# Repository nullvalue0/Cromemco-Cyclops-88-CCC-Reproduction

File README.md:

This is an attempt to reproduce the PCB's for the Cromemco Cyclops digital camera, the 2-board set "88 CCC". The original digital cameras are basically impossible to find. Thankfully there has already been a [reproduction effort for the camera itself](http://wsudbrink.dyndns.org:8080/cyclops/index.html).

The next missing piece then would be the controller boards. While a few of the 88 CCC's have turned up, they are mainly already in collectors hands and still very rare. In several years of trying to find them I haven't been able to nab a set.

With the [Dazzler boards already successfully reproduced](https://forum.vcfed.org/index.php?threads/cromemco-dazzler-replica-project.77906), this seems like a great next project. I'll update this readme as the project progresses.

The 'Original Images' folder contains pictures of the original board set that I've found on various sites.

The 'Original Schematics' folder contains the original manual & schematics for the 88 CCC. I've combined the 2-page schematic into a single image for each board, making it much easier to reference.

The PCB folder will contain the reproduction Kicad files & gerbers for both S-100 boards.

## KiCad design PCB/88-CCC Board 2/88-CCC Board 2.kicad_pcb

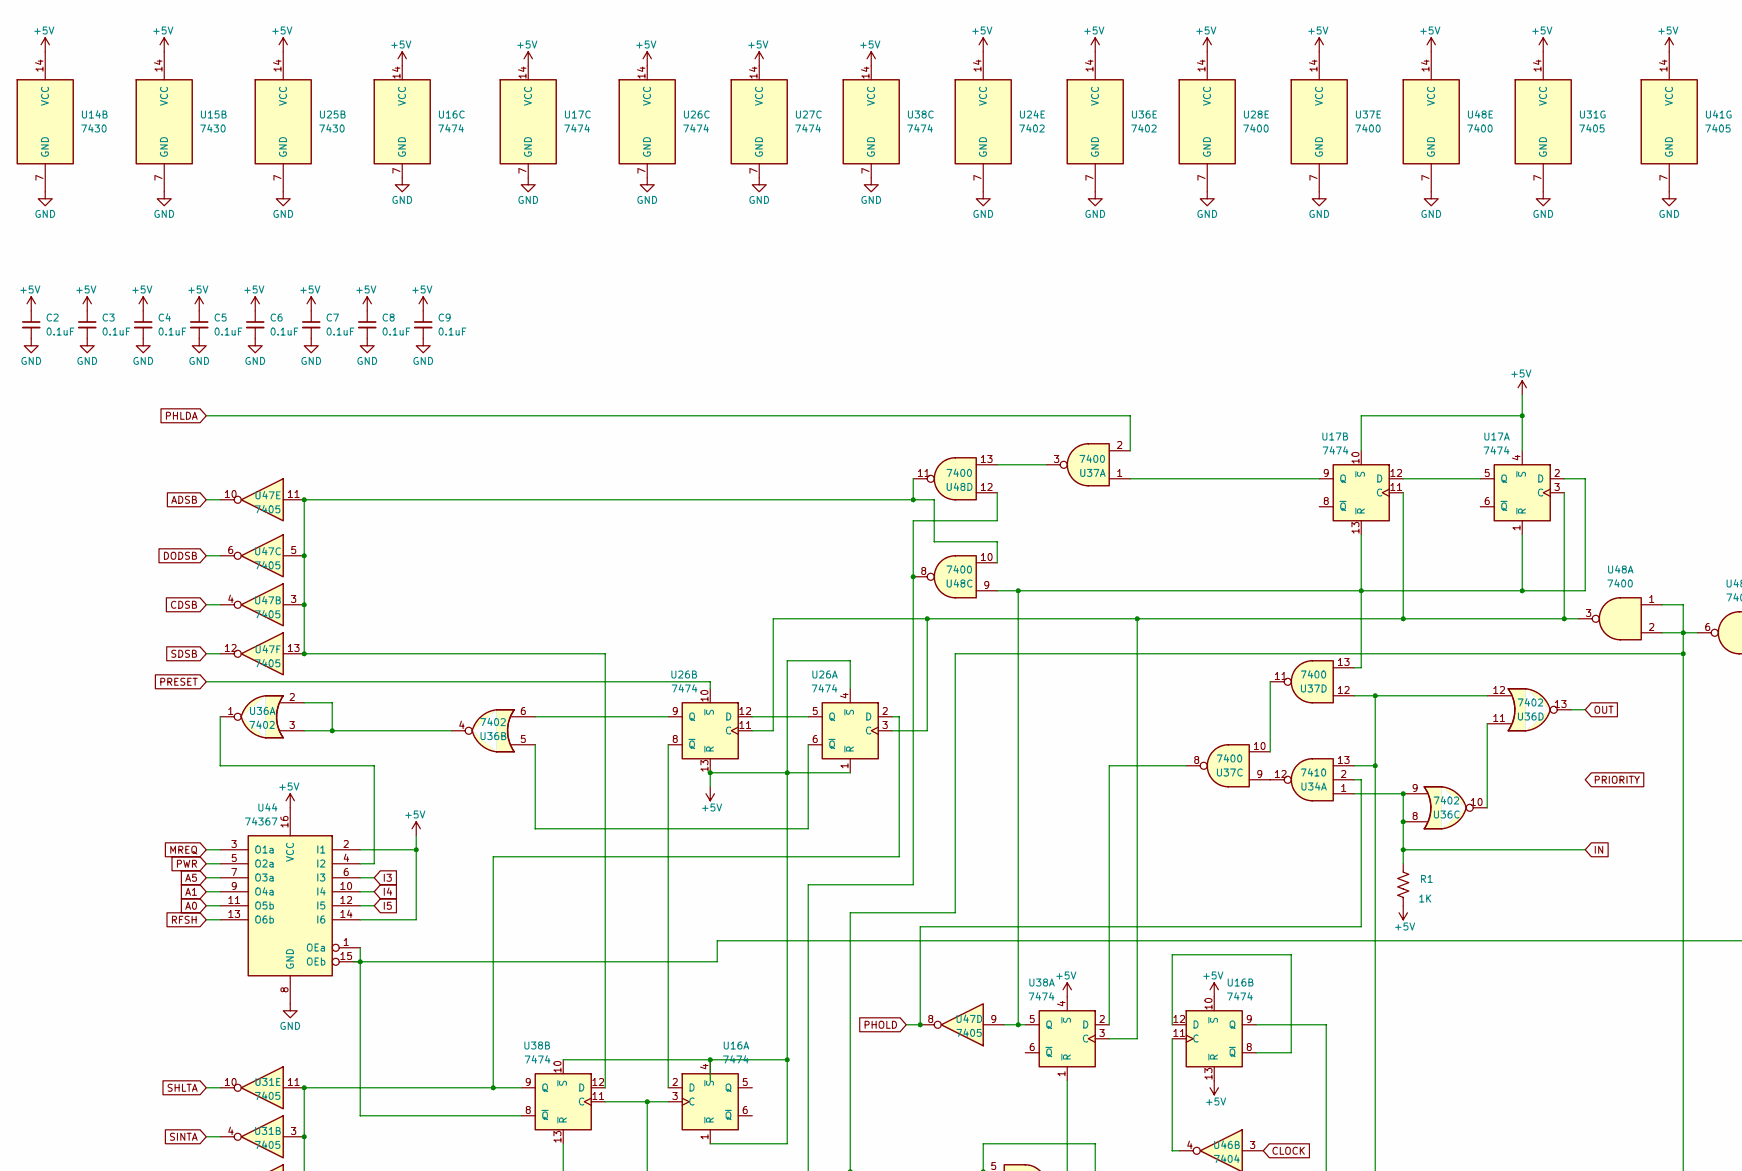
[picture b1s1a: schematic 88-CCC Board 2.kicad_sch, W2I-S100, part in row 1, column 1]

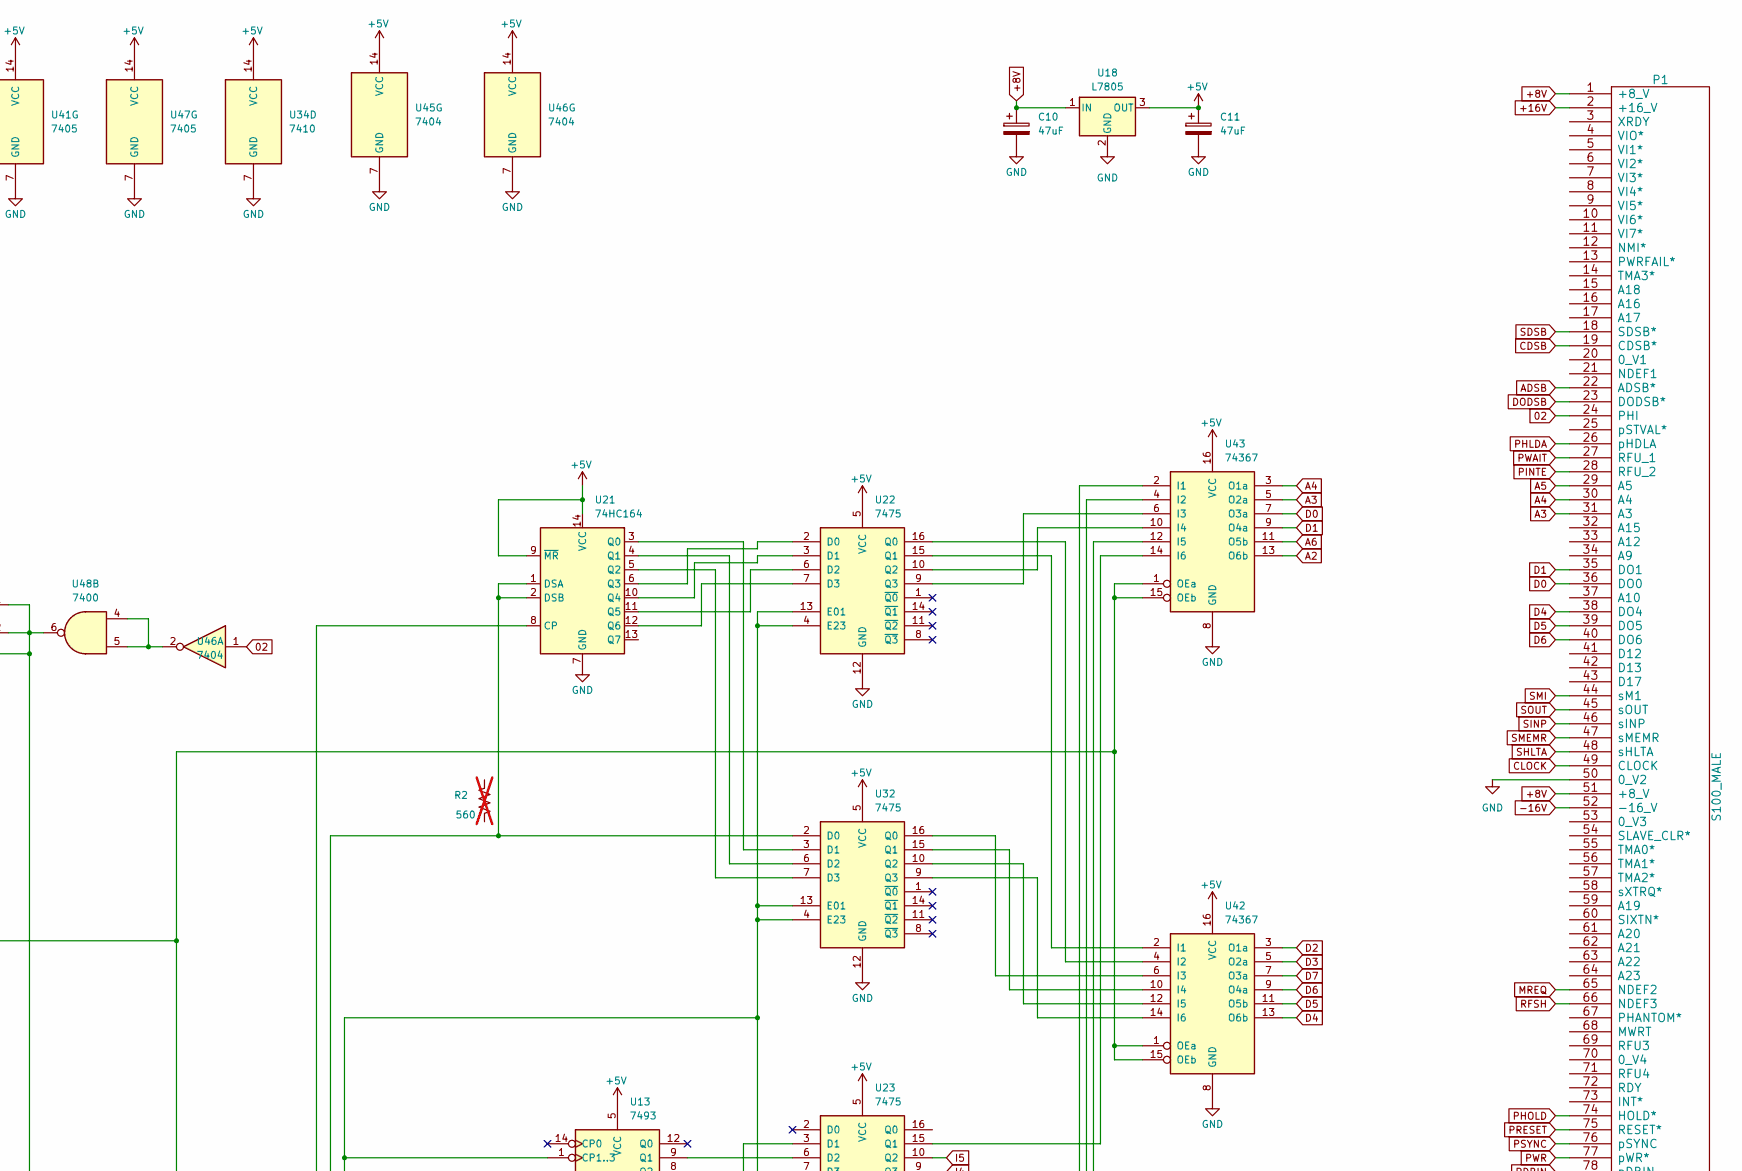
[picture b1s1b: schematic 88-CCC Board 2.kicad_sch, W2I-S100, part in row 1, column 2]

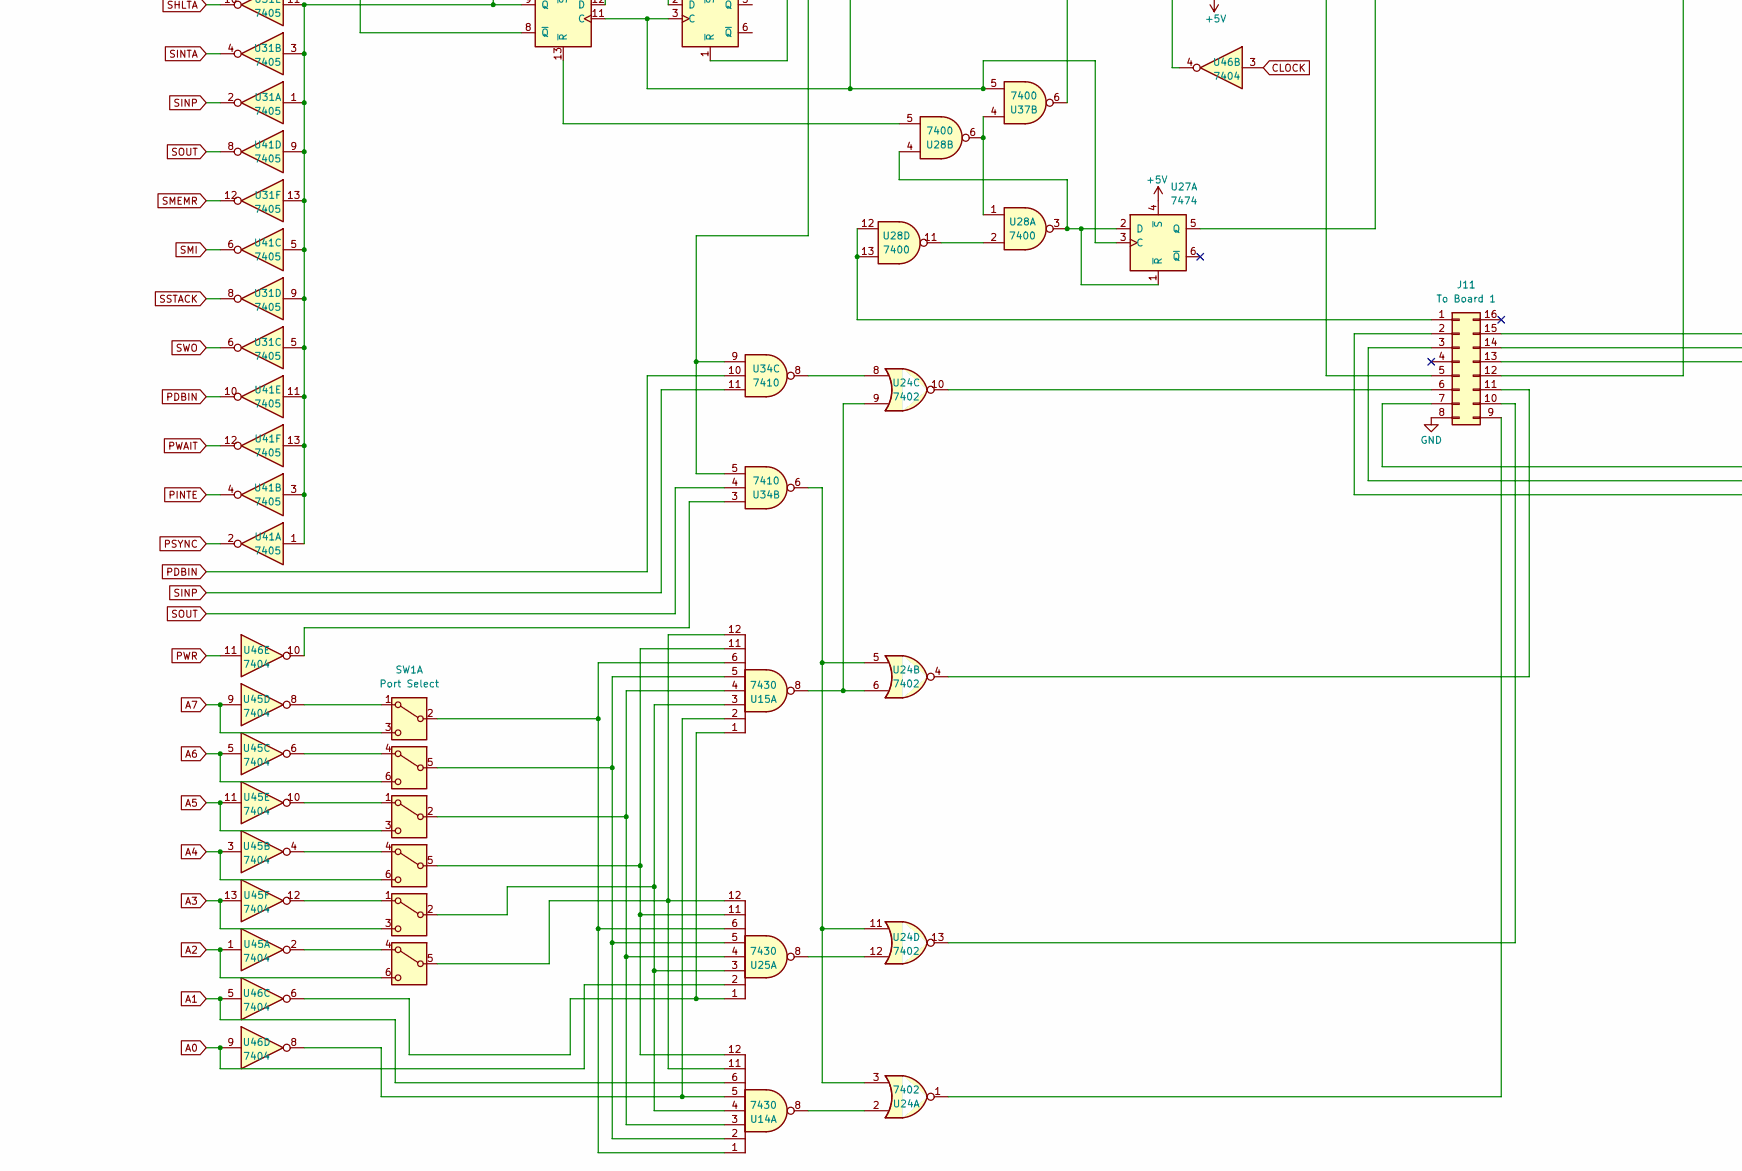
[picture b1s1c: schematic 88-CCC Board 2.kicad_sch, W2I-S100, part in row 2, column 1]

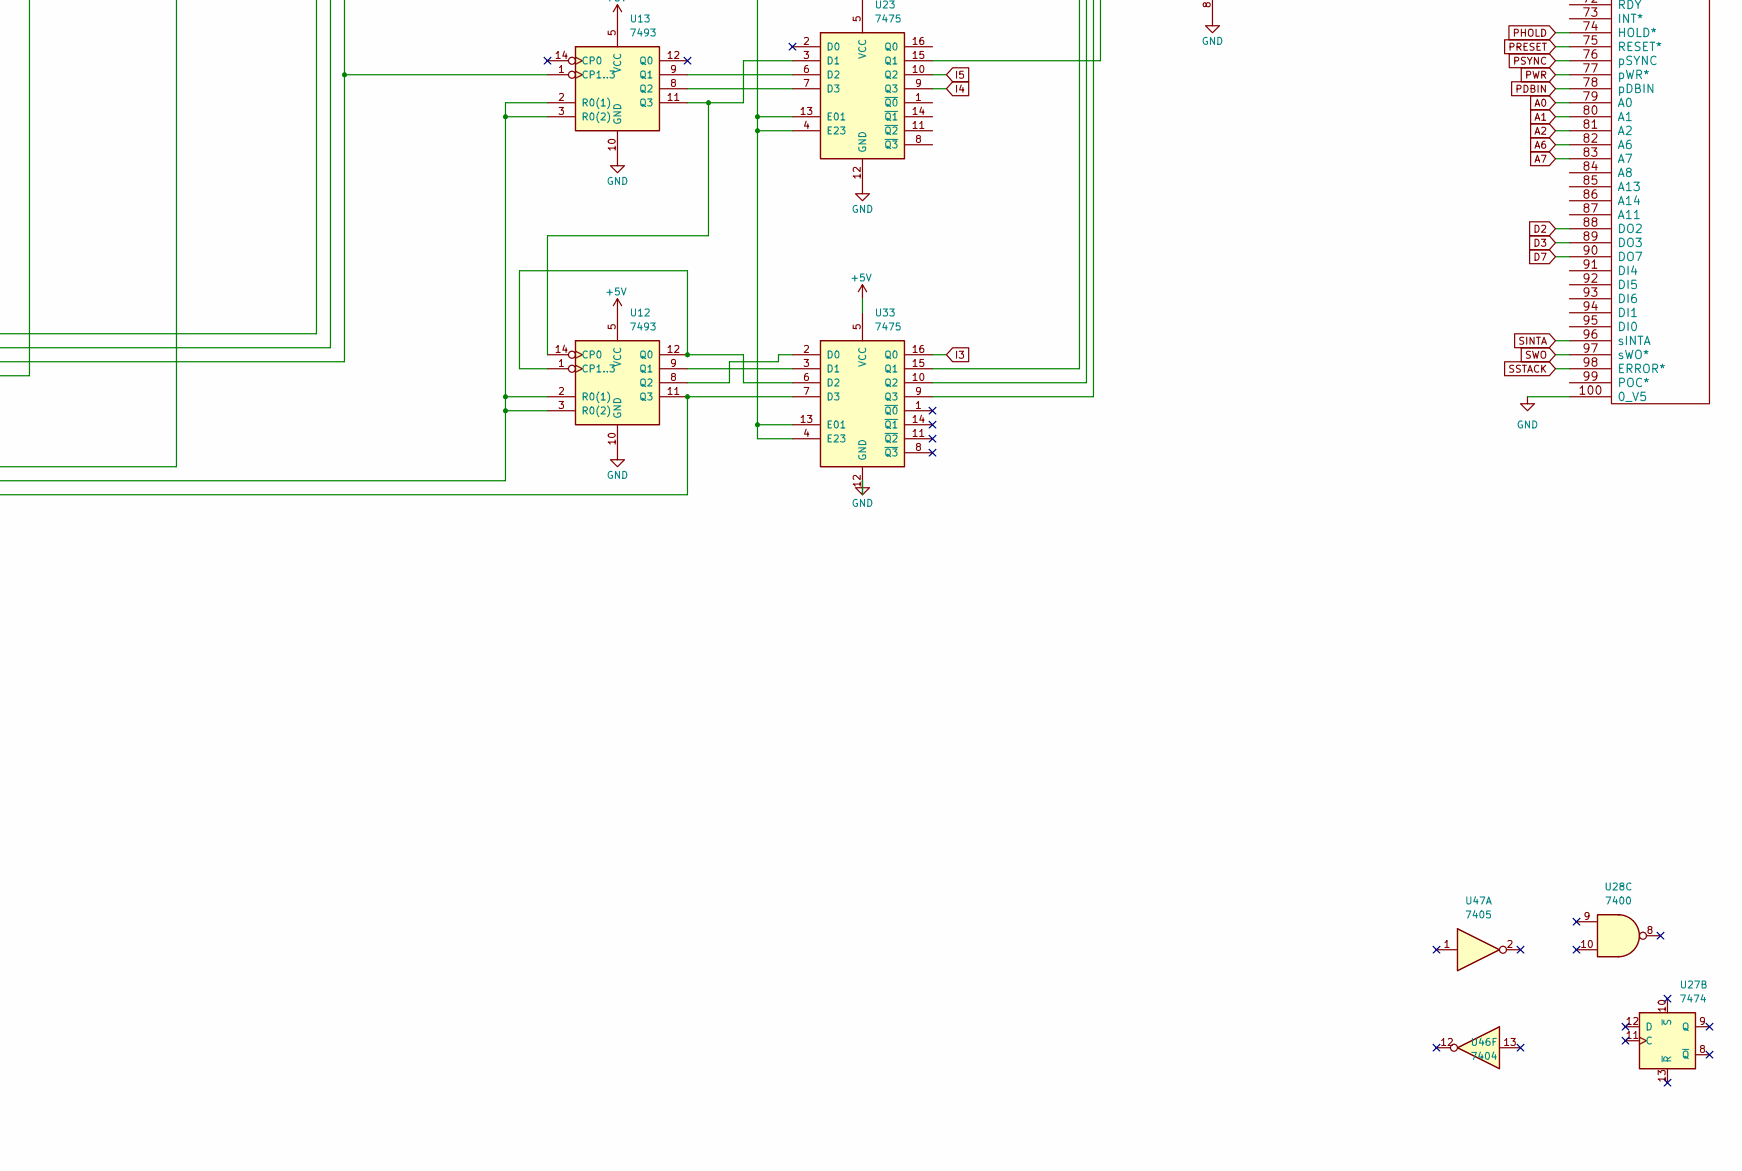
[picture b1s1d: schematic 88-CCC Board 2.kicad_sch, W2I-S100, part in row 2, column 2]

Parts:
C2, C3, C4, C5, C6, C7, C8, C9: 0.1uF; C_Disc_D7.5mm_W5.0mm_P5.00mm
C10, C11: 47uF; C_Axial_L12.0mm_D9.5mm_P20.00mm_Horizontal
J11: To Board 1; DIP-16_W7.62mm
P1: S100_MALE
R1: 1K; R_Axial_DIN0204_L3.6mm_D1.6mm_P7.62mm_Horizontal; LCSC Part C1469
R2: 560; R_Axial_DIN0204_L3.6mm_D1.6mm_P7.62mm_Horizontal; LCSC Part C1469; not fitted
SW1: Port Select; DIP-6_W7.62mm
SW2, SW3: SW_DPDT_x2; DIP-6_W7.62mm
U12, U13: 7493; DIP-14_W7.62mm
U14, U15, U25: 7430; DIP-14_W7.62mm
U16, U17, U26, U27, U38: 7474; DIP-14_W7.62mm
U18: L7805; TO-220-3_Horizontal_TabDown
U21: 74HC164; DIP-14_W7.62mm
U22, U23, U32, U33: 7475; DIP-16_W7.62mm
U24, U36: 7402; DIP-14_W7.62mm
U28, U37, U48: 7400; DIP-14_W7.62mm
U31, U41, U47: 7405; DIP-14_W7.62mm
U34: 7410; DIP-14_W7.62mm
U42, U43, U44: 74367; DIP-16_W7.62mm
U45, U46: 7404; DIP-14_W7.62mm

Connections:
02: P1.24 (PHI), U46.1
+5V: C2.1, C3.1, C4.1, C5.1, C6.1, C7.1, C8.1, C9.1, C11.1, R1.1, U12.5 (VCC), U13.5 (VCC), U14.14 (VCC), U15.14 (VCC), U16.1 (~R), U16.4 (~S), U16.10 (~S), U16.13 (~R), U16.14 (VCC), U17.4 (~S), U17.10 (~S), U17.14 (VCC), U18.3 (OUT), U21.9 (~MR), U21.14 (VCC), U22.5 (VCC), U23.5 (VCC), U24.14 (VCC), U25.14 (VCC), U26.1 (~R), U26.4 (~S), U26.13 (~R), U26.14 (VCC), U27.4 (~S), U27.14 (VCC), U28.14 (VCC), U31.14 (VCC), U32.5 (VCC), U33.5 (VCC), U34.14 (VCC), U36.14 (VCC), U37.14 (VCC), U38.4 (~S), U38.10 (~S), U38.14 (VCC), U41.14 (VCC), U42.16 (VCC), U43.16 (VCC), U44.2 (I1), U44.14 (I6), U44.16 (VCC), U45.14 (VCC), U46.14 (VCC), U47.14 (VCC), U48.14 (VCC)
+8V: C10.1, P1.1 (+8_V), P1.51 (+8_V), U18.1 (IN)
+16V: P1.2 (+16_V)
-16V: P1.52 (-16_V)
A0: P1.79 (A0), U25.2, U44.11 (O5b), U46.9
A1: P1.80 (A1), U14.6, U44.9 (O4a), U46.5
A2: P1.81 (A2), SW3.6 (C), U43.13 (O6b), U45.1
A3: P1.31 (A3), SW3.3 (C), U43.5 (O2a), U45.13
A4: P1.30 (A4), SW2.6 (C), U43.3 (O1a), U45.3
A5: P1.29 (A5), SW2.3 (C), U44.7 (O3a), U45.11
A6: P1.82 (A6), SW1.6 (C), U43.11 (O5b), U45.5
A7: P1.83 (A7), SW1.3 (C), U45.9
ADSB: P1.22 (ADSB*), U47.10
CDSB: P1.19 (CDSB*), U47.4
CLOCK: P1.49 (CLOCK), U46.3
D0: P1.36 (DO0), U43.7 (O3a)
D1: P1.35 (DO1), U43.9 (O4a)
D2: P1.88 (DO2), U42.3 (O1a)
D3: P1.89 (DO3), U42.5 (O2a)
D4: P1.38 (DO4), U42.13 (O6b)
D5: P1.39 (DO5), U42.11 (O5b)
D6: P1.40 (DO6), U42.9 (O4a)
D7: P1.90 (DO7), U42.7 (O3a)
DODSB: P1.23 (DODSB*), U47.6
GND: C2.2, C3.2, C4.2, C5.2, C6.2, C7.2, C8.2, C9.2, C10.2, C11.2, J11.8, P1.50 (0_V2), P1.100 (0_V5), U12.10 (GND), U13.10 (GND), U14.7 (GND), U15.7 (GND), U16.7 (GND), U17.7 (GND), U18.2 (GND), U21.7 (GND), U22.12 (GND), U23.12 (GND), U24.7 (GND), U25.7 (GND), U26.7 (GND), U27.7 (GND), U28.7 (GND), U31.7 (GND), U32.12 (GND), U33.12 (GND), U34.7 (GND), U36.7 (GND), U37.7 (GND), U38.7 (GND), U41.7 (GND), U42.8 (GND), U43.8 (GND), U44.8 (GND), U45.7 (GND), U46.7 (GND), U47.7 (GND), U48.7 (GND)
I3: U33.16 (Q0), U44.6 (I3)
I4: U23.9 (Q3), U44.10 (I4)
I5: U23.10 (Q2), U44.12 (I5)
IN: R1.2, U34.1, U36.8, U36.9
MREQ: P1.65 (NDEF2), U44.3 (O1a)
unnamed: J11.1, U28.12, U28.13
unnamed: J11.2, U12.11 (Q3), U33.7 (D3)
unnamed: J11.3, U12.2 (R0(1)), U12.3 (R0(2)), U13.2 (R0(1)), U13.3 (R0(2))
unnamed: J11.5, U16.9 (Q)
unnamed: J11.6, U24.10
unnamed: J11.7, U38.8 (~Q), U42.1 (OEa), U42.15 (OEb), U43.1 (OEa), U43.15 (OEb), U44.1 (OEa), U44.15 (OEb)
unnamed: J11.9, U24.1
unnamed: J11.10, U24.13
unnamed: J11.11, U24.4
unnamed: J11.12, U16.3 (C), U27.3 (C), U37.5, U38.11 (C), U48.1, U48.2, U48.6
unnamed: J11.13, U13.1 (CP1..3), U22.4 (E23), U22.13 (E01), U23.4 (E23), U23.13 (E01), U32.4 (E23), U32.13 (E01), U33.4 (E23), U33.13 (E01)
unnamed: J11.14, U21.1 (DSA), U21.2 (DSB), U32.2 (D0)
unnamed: J11.15, U21.8 (CP)
unnamed: SW1.1 (A), U45.8
unnamed: SW1.2 (B), U14.1, U15.6, U25.6
unnamed: SW1.4 (A), U45.6
unnamed: SW1.5 (B), U14.2, U15.5, U25.5
unnamed: SW2.1 (A), U45.10
unnamed: SW2.2 (B), U14.3, U15.4, U25.4
unnamed: SW2.4 (A), U45.4
unnamed: SW2.5 (B), U14.12, U15.11, U25.11
unnamed: SW3.1 (A), U45.12
unnamed: SW3.2 (B), U14.4, U15.3, U25.3
unnamed: SW3.4 (A), U45.2
unnamed: SW3.5 (B), U14.11, U15.12, U25.12
unnamed: U12.14 (CP0), U13.11 (Q3), U23.3 (D1)
unnamed: U12.1 (CP1..3), U12.12 (Q0), U33.6 (D2)
unnamed: U12.9 (Q1), U33.3 (D1)
unnamed: U12.8 (Q2), U33.2 (D0)
unnamed: U13.9 (Q1), U23.6 (D2)
unnamed: U13.8 (Q2), U23.7 (D3)
unnamed: U14.5, U15.2, U46.8
unnamed: U14.8, U24.2
unnamed: U15.1, U25.1, U46.6
unnamed: U15.8, U24.6, U24.9
unnamed: U16.2 (D), U26.8 (~Q)
unnamed: U16.11 (C), U46.4
unnamed: U16.8 (~Q), U16.12 (D)
unnamed: U17.3 (C), U17.11 (C), U26.3 (C), U26.11 (C), U38.3 (C), U48.3
unnamed: U17.1 (~R), U17.2 (D), U17.13 (~R), U37.13, U38.5 (Q), U47.9, U48.9
unnamed: U17.5 (Q), U17.12 (D)
unnamed: U17.9 (Q), U37.1
unnamed: U21.3 (Q0), U32.3 (D1)
unnamed: U21.4 (Q1), U32.6 (D2)
unnamed: U21.5 (Q2), U32.7 (D3)
unnamed: U21.6 (Q3), U22.2 (D0)
unnamed: U21.10 (Q4), U22.3 (D1)
unnamed: U21.11 (Q5), U22.6 (D2)
unnamed: U21.12 (Q6), U22.7 (D3)
unnamed: U22.16 (Q0), U42.4 (I2)
unnamed: U22.15 (Q1), U42.2 (I1)
unnamed: U22.10 (Q2), U43.10 (I4)
unnamed: U22.9 (Q3), U43.6 (I3)
unnamed: U23.15 (Q1), U43.14 (I6)
unnamed: U24.8, U34.8
unnamed: U24.3, U24.5, U24.11, U34.6
unnamed: U24.12, U25.8
unnamed: U26.2 (D), U31.1, U31.3, U31.5, U31.9, U31.11, U31.13, U38.9 (Q), U41.1, U41.3, U41.5, U41.9, U41.11, U41.13
unnamed: U26.5 (Q), U26.12 (D)
unnamed: U26.6 (~Q), U36.5
unnamed: U26.9 (Q), U36.6
unnamed: U27.1 (~R), U27.2 (D), U28.3, U28.4
unnamed: U27.5 (Q), U34.13, U36.12, U37.12
unnamed: U28.1, U28.6, U37.4
unnamed: U28.2, U28.11
unnamed: U32.16 (Q0), U42.6 (I3)
unnamed: U32.15 (Q1), U42.10 (I4)
unnamed: U32.10 (Q2), U42.12 (I5)
unnamed: U32.9 (Q3), U42.14 (I6)
unnamed: U33.15 (Q1), U43.2 (I1)
unnamed: U33.10 (Q2), U43.4 (I2)
unnamed: U33.9 (Q3), U43.12 (I5)
unnamed: U34.3, U46.10
unnamed: U34.5, U34.9, U48.8, U48.12
unnamed: U34.12, U37.9
unnamed: U36.2, U36.3, U36.4
unnamed: U36.10, U36.11
unnamed: U37.3, U48.13
unnamed: U37.10, U37.11
unnamed: U37.8, U38.2 (D)
unnamed: U37.6, U38.1 (~R)
unnamed: U38.12 (D), U47.3, U47.5, U47.11, U47.13, U48.10, U48.11
unnamed: U28.5, U38.13 (~R)
unnamed: U36.1, U44.4 (I2)
unnamed: U46.2, U48.4, U48.5
OUT: U36.13
PDBIN: P1.78 (pDBIN), U34.10, U41.10
PHLDA: P1.26 (pHDLA), U37.2
PHOLD: P1.74 (HOLD*), U34.2, U47.8
PINTE: P1.28 (RFU_2), U41.4
PRESET: P1.75 (RESET*), U26.10 (~S)
PSYNC: P1.76 (pSYNC), U41.2
PWAIT: P1.27 (RFU_1), U41.12
PWR: P1.77 (pWR*), U44.5 (O2a), U46.11
RFSH: P1.66 (NDEF3), U44.13 (O6b)
SDSB: P1.18 (SDSB*), U47.12
SHLTA: P1.48 (sHLTA), U31.10
SINP: P1.46 (sINP), U31.2, U34.11
SINTA: P1.96 (sINTA), U31.4
SMEMR: P1.47 (sMEMR), U31.12
SMI: P1.44 (sM1), U41.6
SOUT: P1.45 (sOUT), U34.4, U41.8
SSTACK: P1.98 (ERROR*), U31.8
SWO: P1.97 (sWO*), U31.6

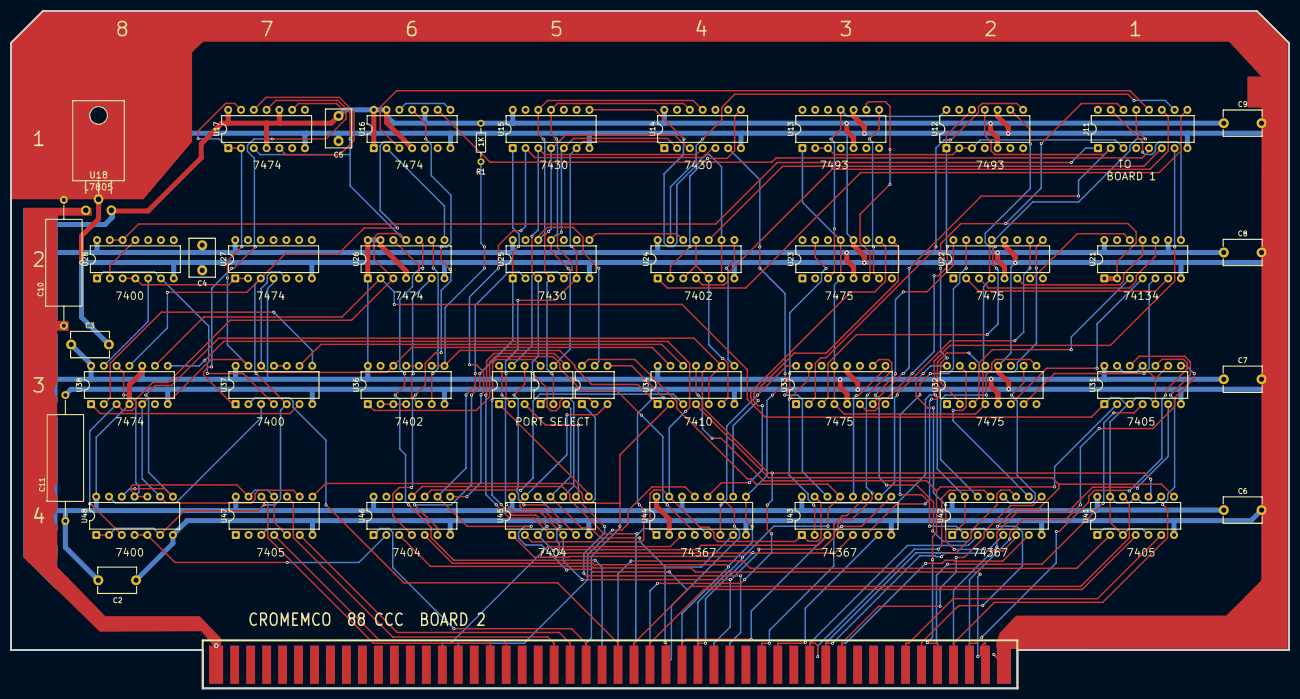
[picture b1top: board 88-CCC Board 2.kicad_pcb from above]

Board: 2 copper layers, 254.0 x 134.6 mm, 46 parts (0 on the bottom side), 132 nets.
